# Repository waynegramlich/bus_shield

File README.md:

# bus_shield
Bus module to connect to an Arduino shield.

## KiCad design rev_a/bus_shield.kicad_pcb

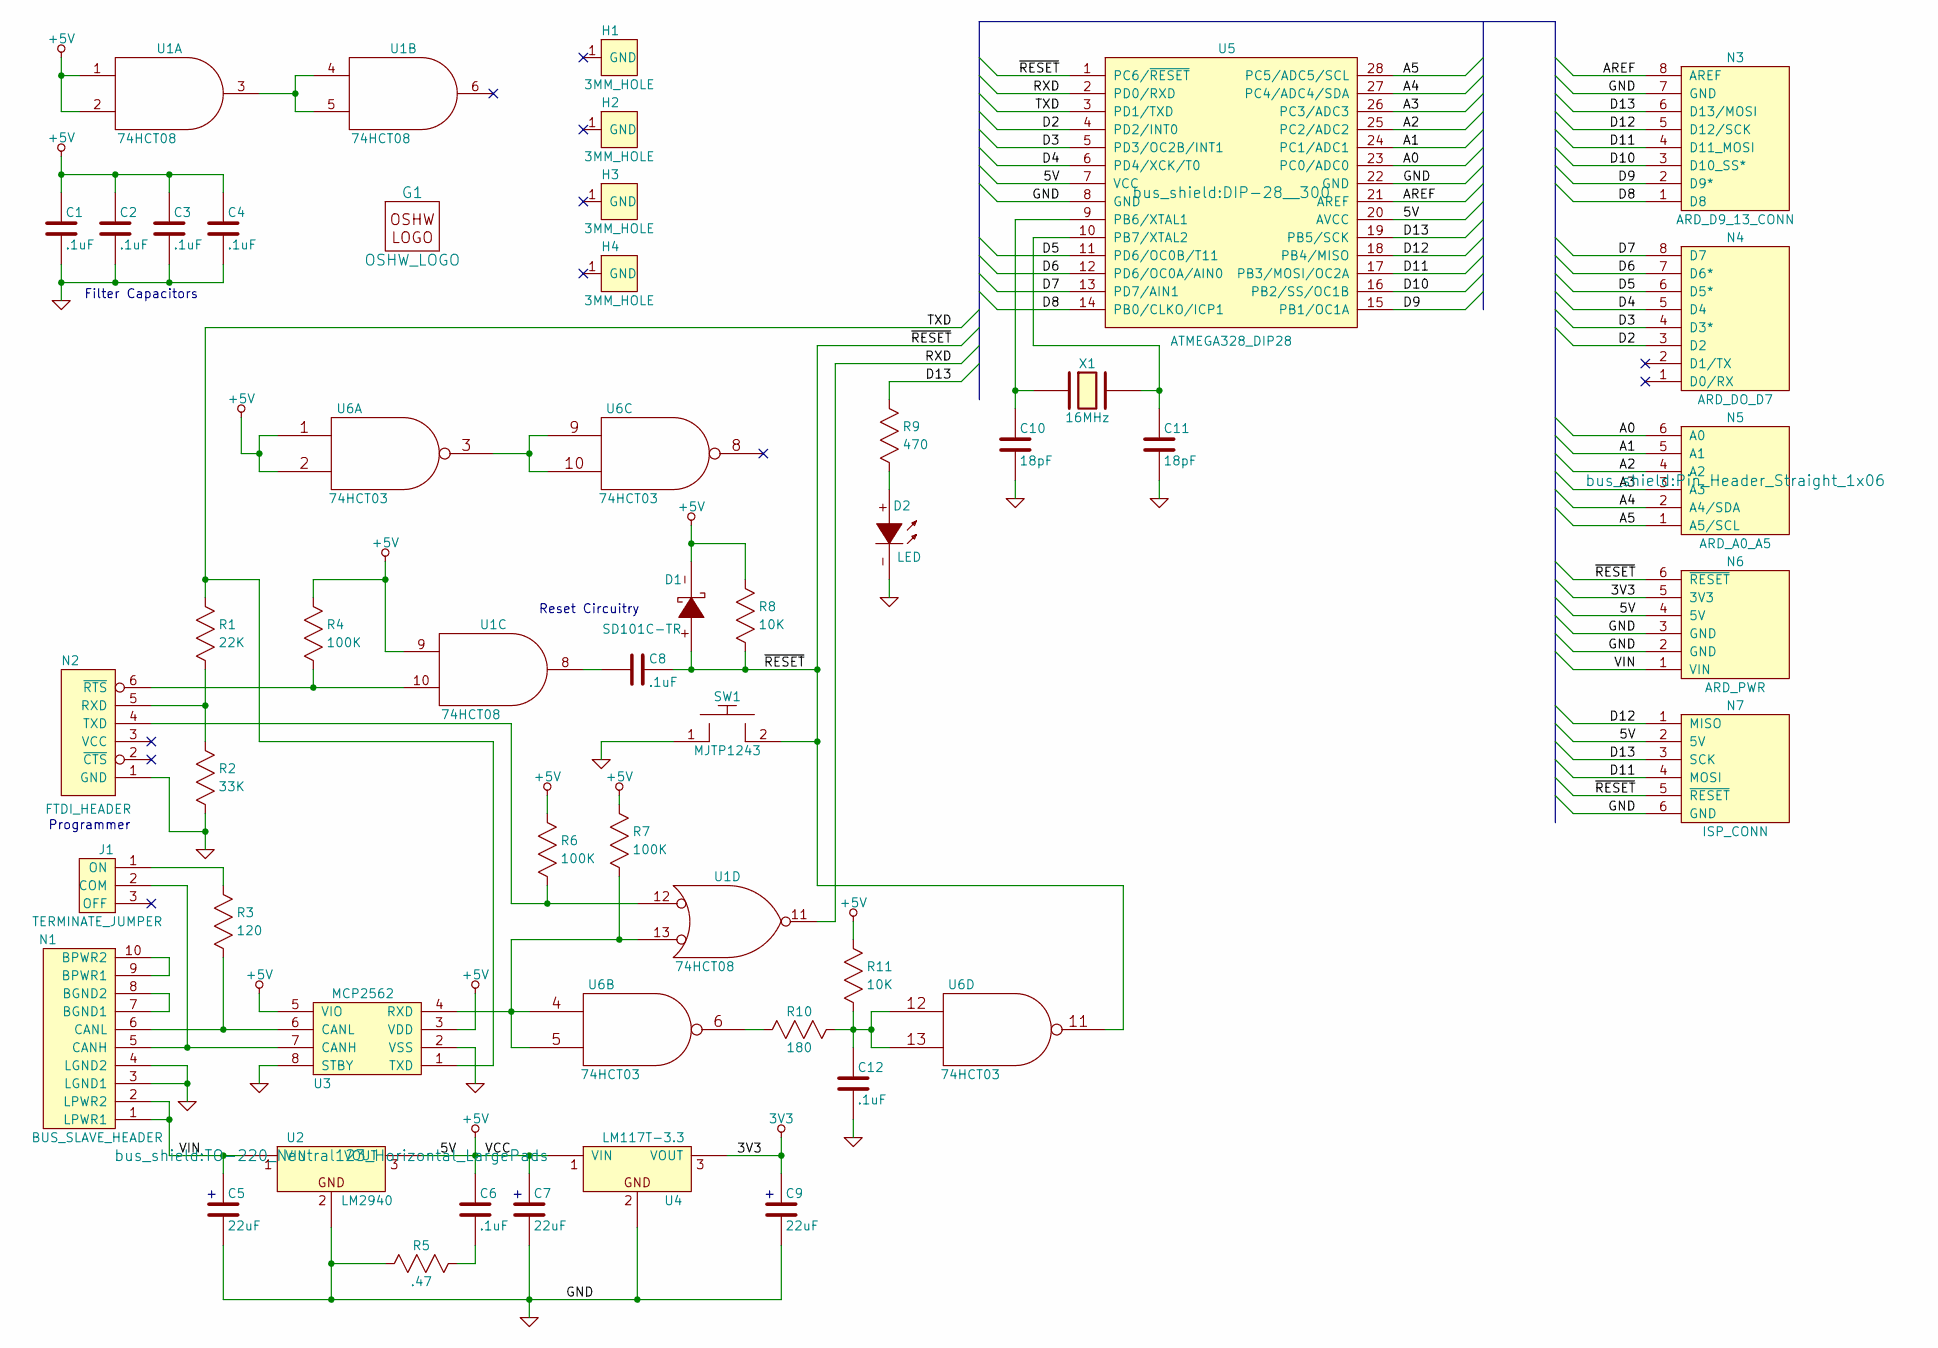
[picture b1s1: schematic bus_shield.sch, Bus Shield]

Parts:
C1, C2, C3, C4, C6, C8, C12: .1uF; Capacitor3MMDiscRM2.5
C5, C7, C9: 22uF; Capacitor3MMDiscRM2.5
C10, C11: 18pF; Capacitor3MMDiscRM2.5
D1: SD101C-TR; Diode_DO-41_SOD81_Horizontal_RM10
D2: LED; T1_LED
G1: OSHW_LOGO; OSHW_LOGO_400mil
H1, H2, H3, H4: 3MM_HOLE; MountingHole_3mm
J1: TERMINATE_JUMPER; Pin_Header_Straight_1x03
N1: BUS_SLAVE_HEADER; Pin_Header_Straight_2x05_Shrouded
N2: FTDI_HEADER; Pin_Header_Straight_1x06
N3: ARD_D9_13_CONN; Pin_Header_Straight_1x08
N4: ARD_DO_D7; Pin_Header_Straight_1x08
N5: ARD_A0_A5; Pin_Header_Straight_1x06
N6: ARD_PWR; Pin_Header_Straight_1x06
N7: ISP_CONN; Pin_Header_Straight_2x03
R1: 22K; Resistor_Horizontal_400
R2: 33K; Resistor_Horizontal_400
R3: 120; Resistor_Horizontal_400
R4, R6, R7: 100K; Resistor_Horizontal_400
R5: .47; Resistor_Horizontal_400
R8, R11: 10K; Resistor_Horizontal_400
R9: 470; Resistor_Horizontal_400
R10: 180; Resistor_Horizontal_400
SW1: MJTP1243; Button_6.5MM
U1: 74HCT08; DIP-14__300
U2: LM2940; TO-220_Neutral123_Horizontal_LargePads
U3: MCP2562; DIP-8__300
U4: LM117T-3.3; TO-220_Neutral123_Horizontal_LargePads
U5: ATMEGA328_DIP28; DIP-28__300
U6: 74HCT03; DIP-14__300
X1: 16MHz; Crystal_HC49-U_Vertical

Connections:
3V3: C9.1, N6.5 (3V3), U4.3 (VOUT)
+5V: C1.1, C2.1, C3.1, C4.1, C6.1, C7.1, D1.-, N6.4 (5V), N7.2 (5V), R4.2, R6.2, R7.2, R8.2, R11.2, U1.1, U1.2, U1.9, U1.14 (VCC), U2.3 (VOUT), U3.3 (VDD), U3.5 (VIO), U4.1 (VIN), U5.7 (VCC), U5.20 (AVCC), U6.1, U6.2, U6.14 (VCC)
/A0: N5.6 (A0), U5.23 (PC0/ADC0)
/A1: N5.5 (A1), U5.24 (PC1/ADC1)
/A2: N5.4 (A2), U5.25 (PC2/ADC2)
/A3: N5.3 (A3), U5.26 (PC3/ADC3)
/A4: N5.2 (A4/SDA), U5.27 (PC4/ADC4/SDA)
/A5: N5.1 (A5/SCL), U5.28 (PC5/ADC5/SCL)
/AREF: N3.8 (AREF), U5.21 (AREF)
/D2: N4.3 (D2), U5.4 (PD2/INT0)
/D3: N4.4 (D3*), U5.5 (PD3/OC2B/INT1)
/D4: N4.5 (D4), U5.6 (PD4/XCK/T0)
/D5: N4.6 (D5*), U5.11 (PD6/OC0B/T11)
/D6: N4.7 (D6*), U5.12 (PD6/OC0A/AIN0)
/D7: N4.8 (D7), U5.13 (PD7/AIN1)
/D8: N3.1 (D8), U5.14 (PB0/CLKO/ICP1)
/D9: N3.2 (D9*), U5.15 (PB1/OC1A)
/D10: N3.3 (D10_SS*), U5.16 (PB2/SS/OC1B)
/D11: N3.4 (D11_MOSI), N7.4 (MOSI), U5.17 (PB3/MOSI/OC2A)
/D12: N3.5 (D12/SCK), N7.1 (MISO), U5.18 (PB4/MISO)
/D13: N3.6 (D13/MOSI), N7.3 (SCK), R9.2, U5.19 (PB5/SCK)
/RXD: U1.11, U5.2 (PD0/RXD)
/TXD: R1.2, U3.1 (TXD), U5.3 (PD1/TXD)
/VIN: C5.1, N1.1 (LPWR1), N1.2 (LPWR2), N6.1 (VIN), U2.1 (VIN)
/~RESET: C8.2, D1.+, N6.6 (~RESET), N7.5 (~RESET), R8.1, SW1.2, U5.1 (PC6/~RESET), U6.11
GND: C1.2, C2.2, C3.2, C4.2, C5.2, C7.2, C9.2, C10.2, C11.2, C12.2, D2.-, N1.3 (LGND1), N1.4 (LGND2), N2.1 (GND), N3.7 (GND), N6.2 (GND), N6.3 (GND), N7.6 (GND), R2.1, R5.1, SW1.1, U1.7 (GND), U2.2, U3.2 (VSS), U3.8 (STBY), U4.2, U5.8 (GND), U5.22 (GND), U6.7 (GND)
unnamed: C6.2, R5.2
unnamed: C8.1, U1.8
unnamed: C10.1, U5.9 (PB6/XTAL1), X1.1
unnamed: C11.1, U5.10 (PB7/XTAL2), X1.2
unnamed: C12.1, R10.2, R11.1, U6.12, U6.13
unnamed: D2.+, R9.1
unnamed: J1.1 (ON), R3.2
unnamed: J1.2 (COM), N1.5 (CANH), U3.7 (CANH)
unnamed: N1.6 (CANL), R3.1, U3.6 (CANL)
unnamed: N1.7 (BGND1), N1.8 (BGND2)
unnamed: N1.9 (BPWR1), N1.10 (BPWR2)
unnamed: N2.4 (TXD), R6.1, U1.12
unnamed: N2.5 (RXD), R1.1, R2.2
unnamed: N2.6 (~RTS), R4.1, U1.10
unnamed: R7.1, U1.13, U3.4 (RXD), U6.4, U6.5
unnamed: R10.1, U6.6
unnamed: U1.3, U1.4, U1.5
unnamed: U6.3, U6.9, U6.10

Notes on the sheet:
Filter Capacitors
Reset Circuitry
Programmer

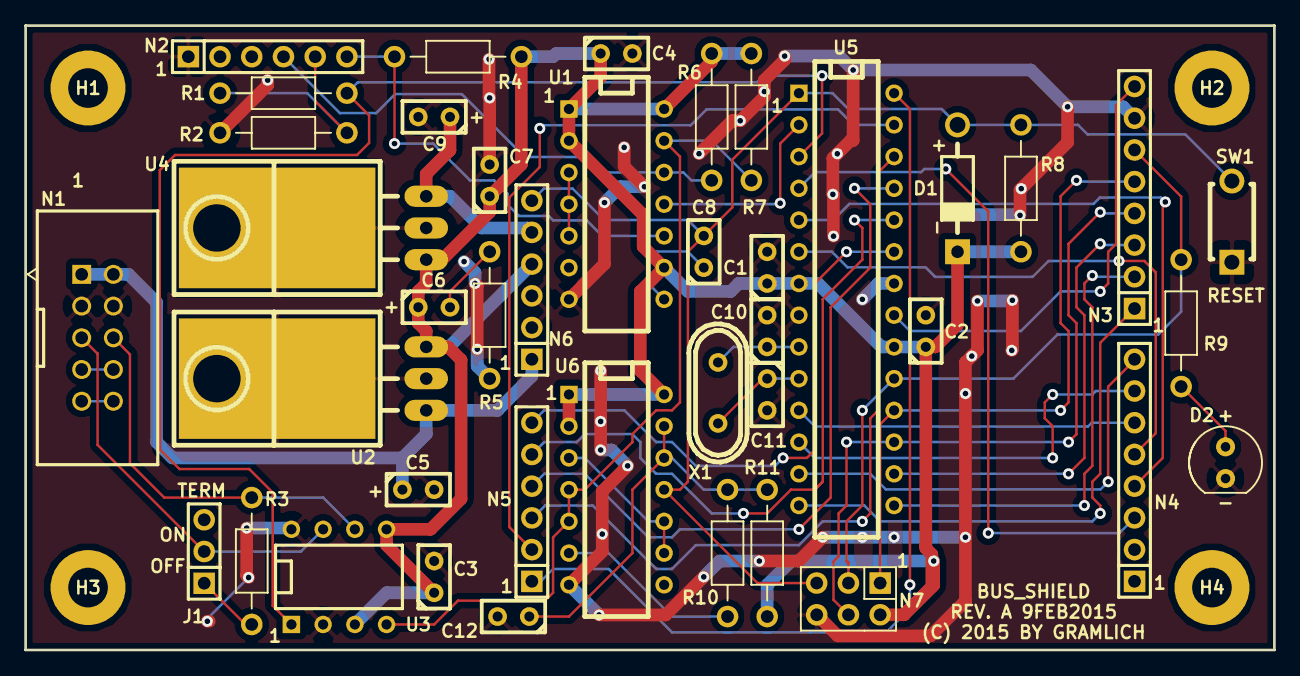
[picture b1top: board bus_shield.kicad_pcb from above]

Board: 2 copper layers, 100.0 x 50.0 mm, 46 parts (1 on the bottom side), 44 nets.

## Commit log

2015-02-02 Got Rev. A ready.
2015-02-09 Reset from bus circuit.
2015-02-13 Split 22uF capacitor into aluminum and tantalum.

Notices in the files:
rev_a/bus_shield.kicad_pcb:
(C) 2015 BY GRAMLICH
